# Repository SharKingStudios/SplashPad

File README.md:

# SplashPad – Because You Deserve More Buttons  

### A Tiny, Glowing, Feature-Packed Macropad for Maximum Efficiency™  

*(Or just a cool way to press "Play" on your music.)*  

---

## Renders 
*Visuals because everyone loves eye candy.*

---
## BOM
All the bits and pieces needed can be found **[here](/BOM.md)**.

---

## What is this?  
It’s a **custom macropad** built with the **Seeed Studio XIAO RP2040**, **KMK firmware**, and **way too many LEDs**. Whether you’re gaming, editing, coding, or just pressing random buttons for fun, this thing’s got you covered.

### Features:
- **3x3 Matrix** – Nine glorious keys to map to whatever your heart desires.
- **Rotary Encoder** – Twist for volume, scroll, or secret hacker functions.
- **Clickable Encoder Button** – Because sometimes, twisting isn’t enough.
- **14 SK6812 Mini LEDs** – Way too many for a macropad this size. But hey, ✨blinkenlights✨.
- **Multiple LED Modes** – Solid, Rainbow, Wave, and Grid Fade, for when you need that cyberpunk aesthetic.
- **KMK Firmware** – Python-powered and open-source, because we like freedom.

---

## How It Works:
This macropad runs **KMK**, which means you get:
- **Custom Keymaps** – Map macros, media keys, or even full-blown scripts.
- **Dynamic Layers** – More functions per button? Yes, please.
- **LED Control** – Pulsing blue? Rainbow waves? Subtle grid fade? Pick your poison.
- **Rotary Encoder Support** – Spin for volume, brightness, scrolling, or **whatever**.

---

## Default Keymap (For the Lazy):
*(Change it if you want, I'm not your boss.)*

### **3x3 Button Layout:**
| Row   | Key 1  | Key 2      | Key 3           |
|-------|--------|------------|-----------------|
| **1** | Rewind | Play/Pause | Fast Forward    |
| **2** | Media  | Calculator | Cmd+R (Refresh) |
| **3** | Left   | Right      | Cmd+L (Lock)    |

### **Rotary Encoder:**
- **Left Turn** → Volume Down
- **Right Turn** → Volume Up
- **Press Button** → Cycle LED modes

---

## How to Use:  
1. **Flash KMK** onto your XIAO RP2040. *(If you don’t know how, Google it.)*
2. **Drop `kb.py` and `main.py`** onto your board.
3. **Plug it in.** Watch the lights do their thing.
4. **Press buttons.** Turn the knob. Make magic happen.

---

## LED Modes:
Because a macropad without RGB is just a fancy calculator.

- **Solid Mode** – A slow, pulsing blue (totally not just lazy coding).
- **Rainbow Mode** – Taste the colors.
- **Wave Mode** – Water flow effect because vibes.
- **Grid Fade Mode** – Simulates sunlight through water. Or something poetic like that.

*(Press the encoder button to switch between them.)*

---

## Why?
I built this macropad for [Hackpad](https://hackpad.hackclub.com/)—an awesome Hack Club YSWS project run by [Alex Ren](https://github.com/qcoral). With a the (hopeful) funding provided by the project, I wanted to create something that’s as practical as it is playful. Whether you're coding, gaming, or just jamming to your favorite tunes, this macropad is my way of saying:

#### why settle for ordinary when you can hack something extraordinary?

## The Biggest Challenge:
I wanted to use nice thick wires for my PCB (0.6mm) and routing all of these took quite a bit of effort. I think the time spent was definitely worth it, as the routing looks *awesome*.

---

## Future Plans (Maybe):  
- OLED Screen? 🤔  
- Bluetooth support? (If I hate myself enough to deal with that.)
- More layers? (How many is too many? Asking for a friend.)
- MIDI support? (Why not turn this into a DJ controller?)

---

## Contribute  
Want to make it better? Open a PR, suggest a feature, or just yell at me on GitHub.

---

## Disclaimer  
This project is 100% free, open-source, and powered by **vibes**. If it breaks, explodes, or opens a black hole, **that’s on you.**

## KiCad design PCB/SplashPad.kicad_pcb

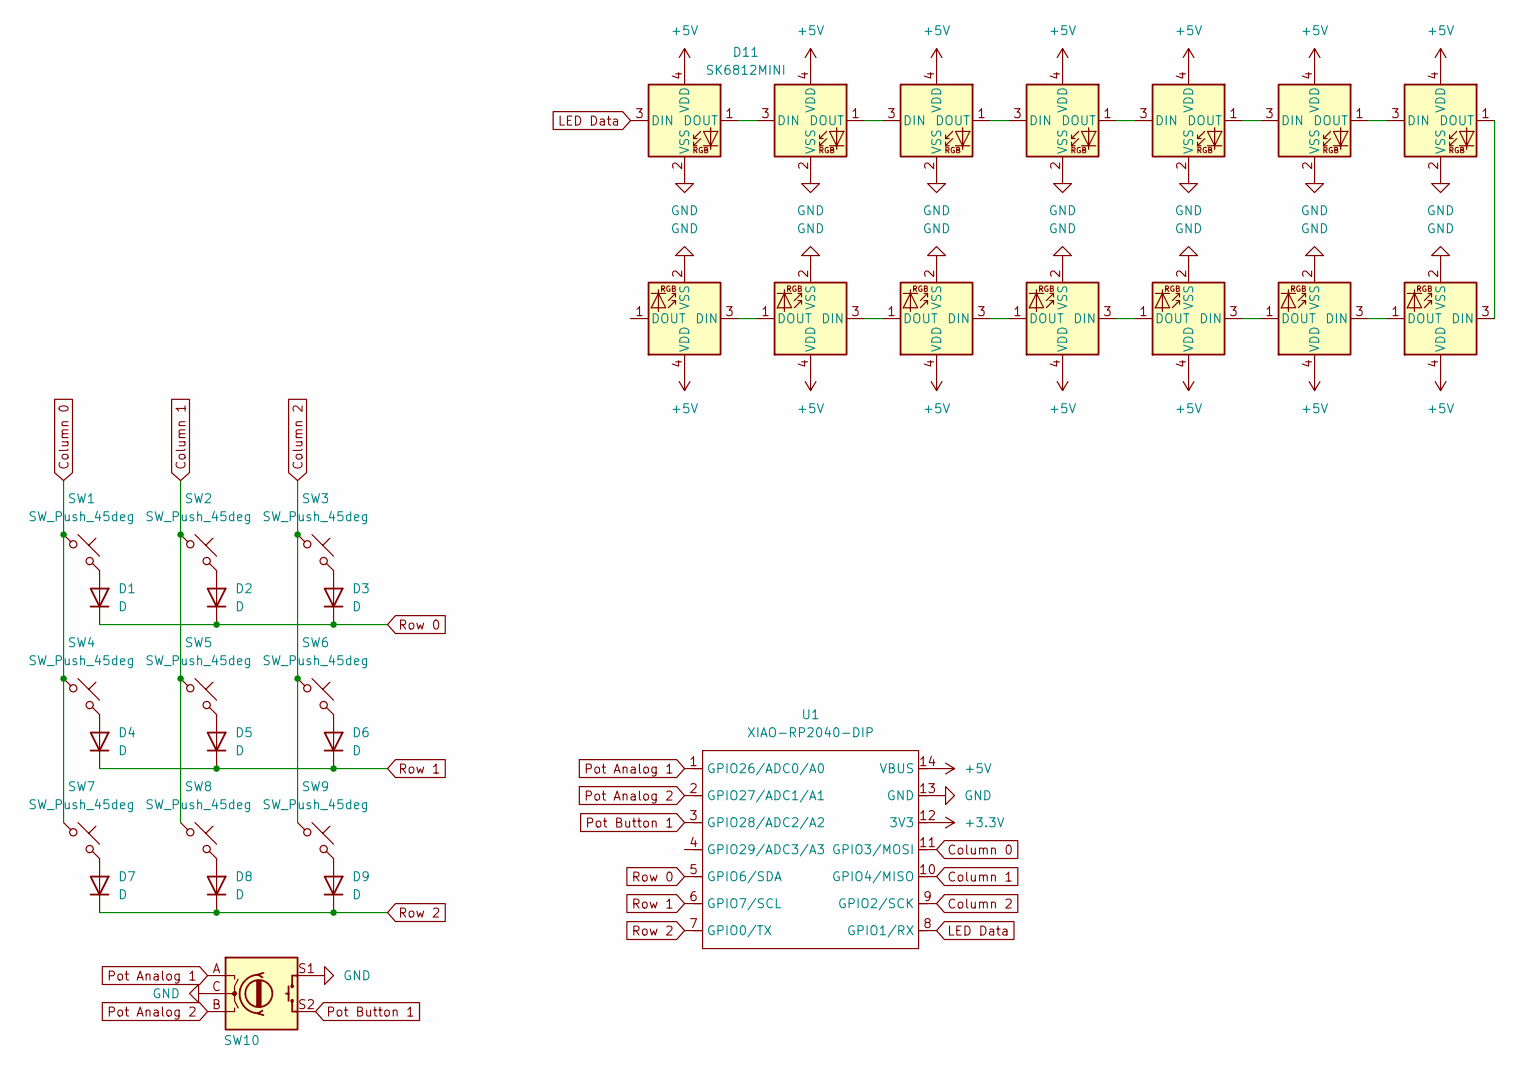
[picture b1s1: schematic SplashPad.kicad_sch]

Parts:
D1, D2, D3, D4, D5, D6, D7, D8, D9: D; D_DO-35_SOD27_P7.62mm_Horizontal
D10, D11, D12, D13, D14, D15, D16, D17, D18, D19, D20, D21, D22, D23: SK6812MINI; LED_SK6812MINI_PLCC4_3.5x3.5mm_P1.75mm
SW1, SW2, SW3, SW4, SW5, SW6, SW7, SW8, SW9: SW_Push_45deg; SW_Cherry_MX_1.00u_PCB
SW10: RotaryEncoder_Switch; RotaryEncoder_Alps_EC11E-Switch_Vertical_H20mm
U1: XIAO-RP2040-DIP

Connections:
+3.3V: U1.12 (3V3)
+5V: D10.4 (VDD), D11.4 (VDD), D12.4 (VDD), D13.4 (VDD), D14.4 (VDD), D15.4 (VDD), D16.4 (VDD), D17.4 (VDD), D18.4 (VDD), D19.4 (VDD), D20.4 (VDD), D21.4 (VDD), D22.4 (VDD), D23.4 (VDD), U1.14 (VBUS)
Column 0: SW1.1, SW4.1, SW7.1, U1.11 (GPIO3/MOSI)
Column 1: SW2.1, SW5.1, SW8.1, U1.10 (GPIO4/MISO)
Column 2: SW3.1, SW6.1, SW9.1, U1.9 (GPIO2/SCK)
GND: D10.2 (VSS), D11.2 (VSS), D12.2 (VSS), D13.2 (VSS), D14.2 (VSS), D15.2 (VSS), D16.2 (VSS), D17.2 (VSS), D18.2 (VSS), D19.2 (VSS), D20.2 (VSS), D21.2 (VSS), D22.2 (VSS), D23.2 (VSS), SW10.C, SW10.S1, U1.13 (GND)
LED Data: D10.3 (DIN), U1.8 (GPIO1/RX)
unnamed: D1.2 (A), SW1.2
unnamed: D2.2 (A), SW2.2
unnamed: D3.2 (A), SW3.2
unnamed: D4.2 (A), SW4.2
unnamed: D5.2 (A), SW5.2
unnamed: D6.2 (A), SW6.2
unnamed: D7.2 (A), SW7.2
unnamed: D8.2 (A), SW8.2
unnamed: D9.2 (A), SW9.2
unnamed: D10.1 (DOUT), D11.3 (DIN)
unnamed: D11.1 (DOUT), D12.3 (DIN)
unnamed: D12.1 (DOUT), D13.3 (DIN)
unnamed: D13.1 (DOUT), D14.3 (DIN)
unnamed: D14.1 (DOUT), D15.3 (DIN)
unnamed: D15.1 (DOUT), D16.3 (DIN)
unnamed: D16.1 (DOUT), D17.3 (DIN)
unnamed: D17.1 (DOUT), D18.3 (DIN)
unnamed: D18.1 (DOUT), D19.3 (DIN)
unnamed: D19.1 (DOUT), D20.3 (DIN)
unnamed: D20.1 (DOUT), D21.3 (DIN)
unnamed: D21.1 (DOUT), D22.3 (DIN)
unnamed: D22.1 (DOUT), D23.3 (DIN)
Pot Analog 1: SW10.A, U1.1 (GPIO26/ADC0/A0)
Pot Analog 2: SW10.B, U1.2 (GPIO27/ADC1/A1)
Pot Button 1: SW10.S2, U1.3 (GPIO28/ADC2/A2)
Row 0: D1.1 (K), D2.1 (K), D3.1 (K), U1.5 (GPIO6/SDA)
Row 1: D4.1 (K), D5.1 (K), D6.1 (K), U1.6 (GPIO7/SCL)
Row 2: D7.1 (K), D8.1 (K), D9.1 (K), U1.7 (GPIO0/TX)

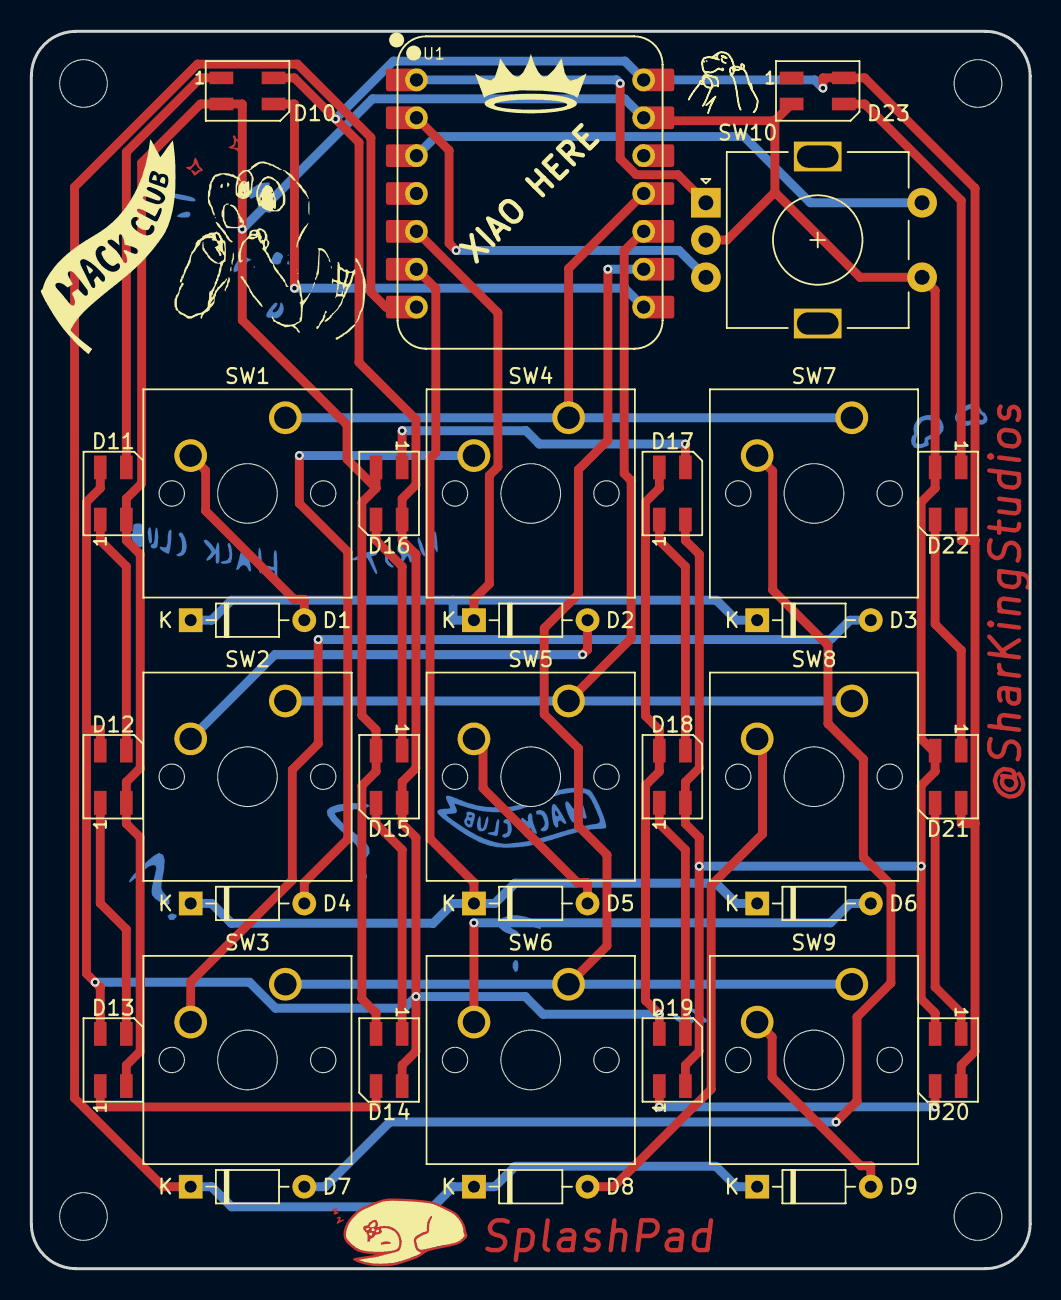
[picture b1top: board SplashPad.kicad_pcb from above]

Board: 2 copper layers, 67.0 x 83.0 mm, 38 parts (0 on the bottom side), 34 nets.

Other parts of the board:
HOLE1, HOLE2, HOLE3, HOLE4: 3.2mm_M3; MountingHole_3.2mm_M3

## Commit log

2025-02-08 "minor changes"
    relearned KiCAD lol
2025-02-09 fine tuning
2025-02-09 The Fun Part
2025-02-09 encoder fix
2025-02-09 trace fix
2025-02-13 Awesome Silkscreen Art!
2025-02-13 KMK Firmware
    Surprisingly easy
2025-02-16 The submission
    Pretty sure this is it.
    :)
2025-02-16 README Updates
    Added some more pictures ;)
2025-02-16 Update README
    Its the last time I swear
2025-02-16 Final Updates
    This is the last one I swear
2025-03-10 LED Voltage Fix
    I thought they worked at 3.3v oopsies
    I also had the encoder wired wrong and fixed that.
2025-06-30 Created Project Logo
2025-12-04 QMK Firmware!
2025-12-04 QMK Update
